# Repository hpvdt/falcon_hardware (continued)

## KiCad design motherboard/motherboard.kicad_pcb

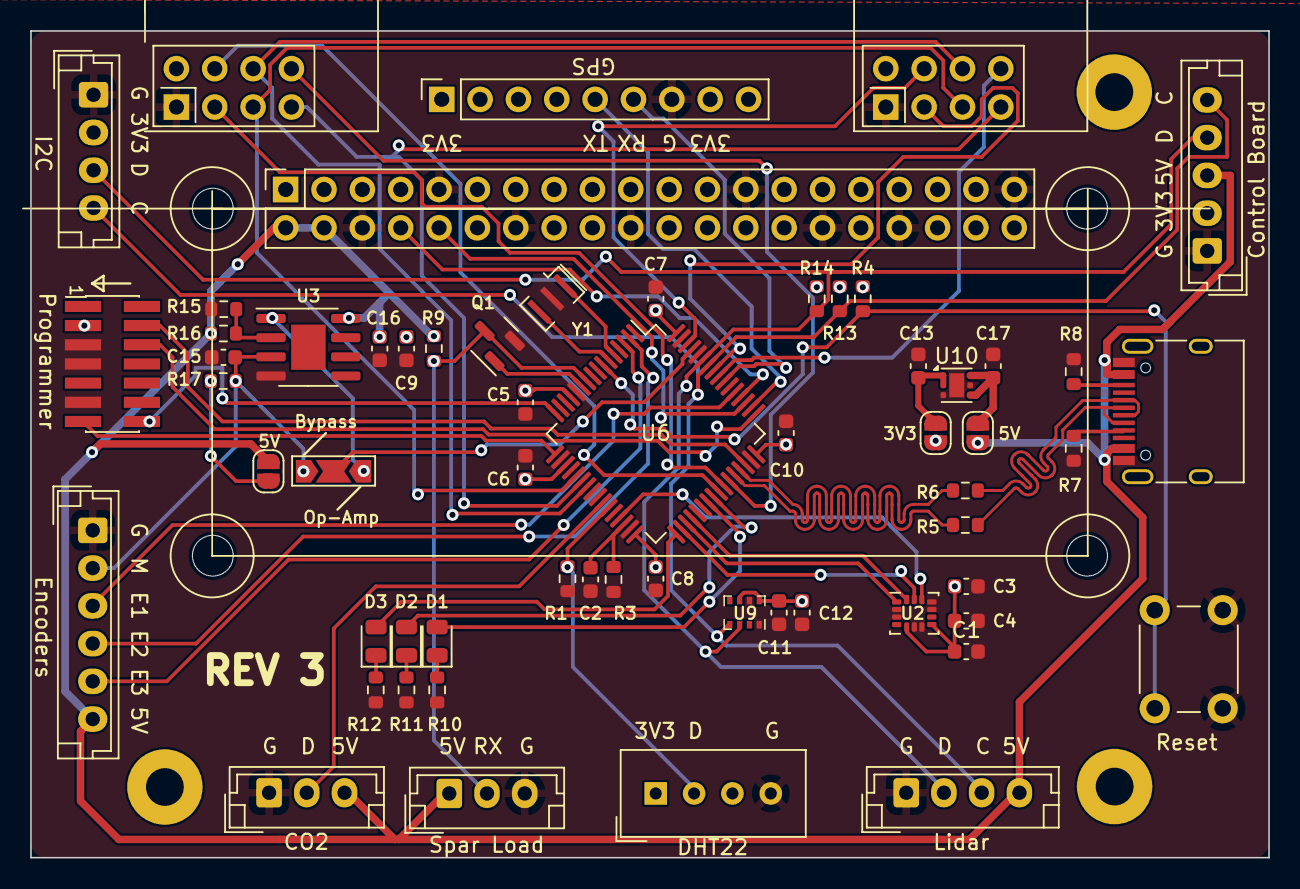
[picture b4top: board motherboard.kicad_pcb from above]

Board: 2 copper layers, 82.0 x 54.8 mm, 67 parts (0 on the bottom side), 56 nets.

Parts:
C1, C9, C15: 10n; C_0603_1608Metric
C2: 4.7u; C_0603_1608Metric
C3: 2.2u; C_0603_1608Metric
C4, C5, C6, C7, C8, C11, C12, C16: 100n; C_0603_1608Metric
C10: 1u; C_0603_1608Metric
C13, C17: 0.22u; C_0603_1608Metric
D1, D2, D3: LED; LED_0805_2012Metric
H1, H3, H4: MountingHole; MountingHole_2.5mm_Pad
H5, H6, H7, H8: MountingHole; MountingHole_2.7mm_M2.5
J1: Raspberry_Pi_2_3 ANT; PinSocket_2x20_P2.54mm_Vertical
J2: Conn_ST_STDC14; PinHeader_2x07_P1.27mm_Vertical_SMD
J3: Battery / Pitot/ Orientation; JST_EH_B4B-EH-A_1x04_P2.50mm_Vertical
J4: c02 censor; JST_EH_B3B-EH-A_1x03_P2.50mm_Vertical
J5: shaftencorder; JST_EH_B6B-EH-A_1x06_P2.50mm_Vertical
J6: USB_C_Receptacle_USB2.0; USB_C_Receptacle_HRO_TYPE-C-31-M-12
J7: SparLoad; JST_EH_B3B-EH-A_1x03_P2.50mm_Vertical
J8: lidar; JST_EH_B4B-EH-A_1x04_P2.50mm_Vertical
J9: Control Board; JST_EH_B5B-EH-A_1x05_P2.50mm_Vertical
JP1: Jumper_3_Open; SolderJumper-3_P2.0mm_Open_TrianglePad1.0x1.5mm_NumberLabels
JP4: 5V; SolderJumper-2_P1.3mm_Open_RoundedPad1.0x1.5mm
JP5, JP6: Jumper_2_Open; SolderJumper-2_P1.3mm_Open_RoundedPad1.0x1.5mm
Q1: 2N7002K; SOT-23
R1, R3: 100k; R_0603_1608Metric
R4, R13, R14: 10k; R_0603_1608Metric
R5, R6: 22R; R_0603_1608Metric
R7, R8: 5.1K; R_0603_1608Metric
R9: 5.6k; R_0603_1608Metric
R10, R11, R12: 130R; R_0603_1608Metric
R15: 1k; R_0603_1608Metric
R16: 20k; R_0603_1608Metric
R17: 470R; R_0603_1608Metric
SW1: MCU_RST; SW_PUSH_6mm_H4.3mm
U2: IMU; LGA-14_3x2.5mm_P0.5mm_LayoutBorder3x4y
U3: LM358; SOIC-8-1EP_3.9x4.9mm_P1.27mm_EP2.29x3mm
U4: GPS module; PinSocket_1x09_P2.54mm_Vertical
U5: DHT11(DHT22); Aosong_DHT11_5.5x12.0_P2.54mm
U6: STM32F412RETx; LQFP-64_10x10mm_P0.5mm
U7: nRF24L01-telemetry-INTERIOR; nRF24L01_Breakout
U8: nRF24L01-telemetry-EXTERIOR; nRF24L01_Breakout
U9: DPS310 - barometer; Bosch_LGA-8_2x2.5mm_P0.65mm_ClockwisePinNumbering
U10: TLV76733DRVx; WSON-6-1EP_2x2mm_P0.65mm_EP1x1.6mm
Y1: 8M; Resonator_SMD_Murata_CSTxExxV-3Pin_3.0x1.1mm

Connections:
+3.3V: C1.1, C3.1, C4.1, C5.2, C6.2, C7.2, C8.2, C9.2, C10.2, C11.1, C12.1, J2.3 (VCC), J3.2, J9.2, JP5.2 (B), R4.2, R13.1, R14.1, U2.5 (VDD_{IO}), U2.8 (VDD), U4.1 (3.3V), U4.8 (VIN), U5.1 (VDD), U6.13 (VDDA), U6.19 (VDD), U6.32 (VDD), U6.48 (VDD), U6.64 (VDD), U7.2 (VCC), U8.2 (VCC), U9.6 (V_{DDIO}), U9.8 (V_{DD})
+5V: C16.1, J1.2 (5V), J1.4 (5V), J4.3, J5.6, J6.A4 (VBUS), J6.A9 (VBUS), J6.B4 (VBUS), J6.B9 (VBUS), J7.1, J8.4, J9.3, JP4.2 (B), JP6.1 (A), R9.1, R16.1, U3.8 (V+)
/CO_{2}: J4.2, U6.26 (PB0)
/D+: J6.A6 (D+), J6.B6 (D+), R6.2
/D-: J6.A7 (D-), J6.B7 (D-), R5.2
/DHT22: R1.2, U5.2 (DATA), U6.27 (PB1)
/ENC1: J5.3, U6.53 (PC12)
/ENC2: J5.4, U6.2 (PC13)
/ENC3: J5.5, U6.3 (PC14)
/I2C_{SCK}: J3.4, J8.3, J9.5, R13.2, U6.58 (PB6), U9.4 (SCK)
/I2C_{SDA}: J3.3, J8.2, J9.4, R14.2, U6.59 (PB7), U9.3 (SDI)
/IMU_{CS}: U2.12 (CS), U6.29 (PB10)
/LED1: D1.2 (A), U6.39 (PC8)
/LED2: D2.2 (A), U6.40 (PC9)
/LED3: D3.2 (A), U6.33 (PB12)
/OneWire_{RX}: J7.2, Q1.3 (D), R9.2, U6.10 (PC2)
/OneWire_{TX}: Q1.1 (G), U6.11 (PC3)
/RST: R4.1, SW1.2, U6.7 (NRST)
/SHAFTENC IN: C15.1, J5.2, JP1.1 (A), R17.2, U3.3 (+)
/SHAFTENC OUT: JP1.2 (C), U6.61 (PB8)
/SPI1MISO: U6.22 (PA6), U7.7 (MISO), U8.7 (MISO)
/SPI1MOSI: U6.23 (PA7), U7.6 (MOSI), U8.6 (MOSI)
/SPI1SCK: U6.21 (PA5), U7.5 (SCK), U8.5 (SCK)
/SPI2MISO: U2.1 (SDO), U6.35 (PB14)
/SPI2MOSI: U2.14 (SDI), U6.36 (PB15)
/SPI2SCK: U2.13 (SCK), U6.34 (PB13)
/SWCLK: J2.6 (JCLK/SWCLK), U6.49 (PA14)
/SWDIO: J2.4 (JTMS/SWDIO), U6.46 (PA13)
/TELE_{CE}-E: U6.42 (PA9), U8.3 (CE)
/TELE_{CE}-int: U6.57 (PB5), U7.3 (CE)
/TELE_{CS}-E: U6.41 (PA8), U8.4 (~CSN)
/TELE_{CS}-int: U6.62 (PB9), U7.4 (~CSN)
/TELE_{IRQ}-E: U6.43 (PA10), U8.8 (IRQ)
/TELE_{IRQ}-int: U6.56 (PB4), U7.8 (IRQ)
/USART1_{RX}: U4.6 (RX), U6.55 (PB3)
/USART1_{TX}: U4.5 (TX), U6.50 (PA15)
/USART2_{RX}: J2.13 (VCP_RX), U6.17 (PA3)
/USART2_{TX}: J2.14 (VCP_TX), U6.16 (PA2)
/USART3_{RX}: J1.8 (GPIO14/TXD), U6.52 (PC11)
/USART3_{TX}: J1.10 (GPIO15/RXD), U6.51 (PC10)
/USB+: R6.1, U6.45 (PA12)
/USB-: R5.1, U6.44 (PA11)
GND: C1.2, C2.2, C3.2, C4.2, C5.1, C6.1, C7.1, C8.1, C9.1, C10.1, C11.2, C12.2, C13.2, C15.2, C16.2, C17.2, J1.6 (GND), J1.9 (GND), J1.14 (GND), J1.20 (GND), J1.25 (GND), J1.30 (GND), J1.34 (GND), J1.39 (GND), J2.5 (GND), J2.7 (GND), J2.11 (GNDDetect), J3.1, J4.1, J5.1, J6.A1 (GND), J6.A12 (GND), J6.B1 (GND), J6.B12 (GND), J7.3, J8.1, J9.1, Q1.2 (S), R1.1, R3.1, R7.1, R8.1, R10.1, R11.1, R12.2, R15.2, SW1.1, U2.2 (RESV), U2.3 (RESV), U2.6 (GND), U2.7 (RESV), U2.10 (RESV), U2.11 (RESV), U3.4 (V-), U4.7 (GND), U5.4 (GND), U6.12 (VSSA), U6.18 (VSS), U6.31 (VSS), U6.47 (VSS), U6.60 (BOOT0), U6.63 (VSS), U7.1 (GND), U8.1 (GND), U9.1 (GND), U9.7 (GND), U10.3 (GND), U10.5 (GND), U10.7 (PAD), Y1.2
unnamed: D1.1 (K), R10.2
unnamed: D2.1 (K), R11.2
unnamed: D3.1 (K), R12.1
unnamed: J6.A5 (CC1), R7.2
unnamed: J6.B5 (CC2), R8.2
unnamed: JP1.3 (B), U3.1
unnamed: JP4.1 (A), R17.1
unnamed: C13.1, JP5.1 (A), U10.1 (OUT), U10.2 (SNS)
unnamed: C17.1, JP6.2 (B), U10.4 (EN), U10.6 (IN)
unnamed: R15.1, R16.2, U3.2 (-)
unnamed: U6.5 (PH0), Y1.1
unnamed: U6.6 (PH1), Y1.3
unnamed: C2.1, R3.2, U6.30 (VCAP_1)

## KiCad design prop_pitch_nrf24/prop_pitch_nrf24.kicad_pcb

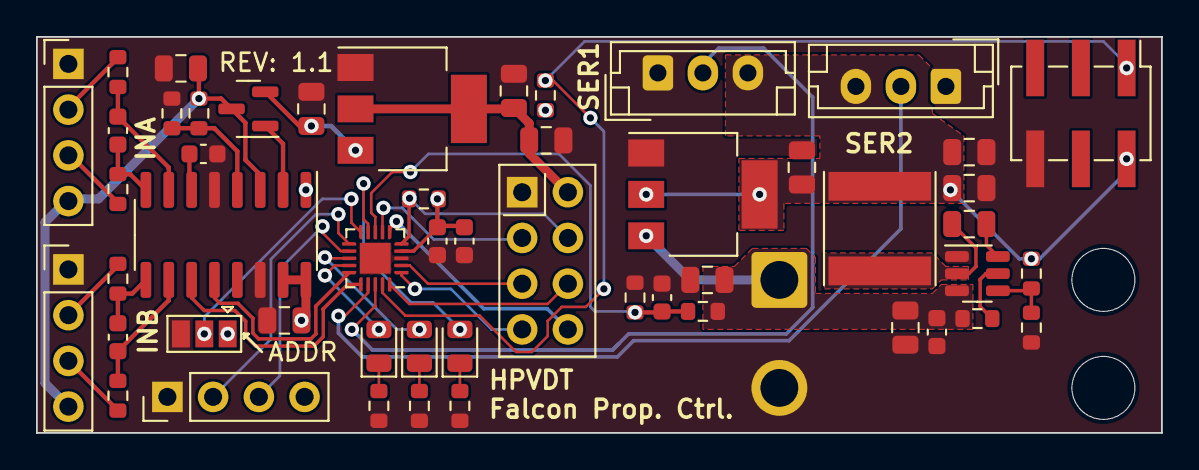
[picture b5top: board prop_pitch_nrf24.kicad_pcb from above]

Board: 2 copper layers, 62.5 x 22.0 mm, 53 parts (1 on the bottom side), 41 nets.

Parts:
BT1: Battery; SolderWire-1.5sqmm_1x02_P6mm_D1.7mm_OD3mm_Relief
C1, C2, C3, C5, C9, C11: 100n; C_0603_1608Metric
C4, C6, C10, C15, C16, C18: 10u; C_0805_2012Metric
C7: 10n; C_0603_1608Metric
C12: 100n; C_0805_2012Metric
C13, C14, C19, C20: 22u; C_0805_2012Metric
D1, D2, D3: LED; LED_0805_2012Metric
J1: LOAD1; PinHeader_1x04_P2.54mm_Vertical
J2: LOAD2; PinHeader_1x04_P2.54mm_Vertical
J3: AVR-UPDI-6; PinHeader_2x03_P2.54mm_Vertical_SMD
J4: SERVO2; JST_EH_B3B-EH-A_1x03_P2.50mm_Vertical
J5: SERVO1; JST_EH_B3B-EH-A_1x03_P2.50mm_Vertical
J6: SERIAL; PinHeader_1x04_P2.54mm_Vertical
JP1: ADDRESS; SolderJumper-3_P1.3mm_Open_Pad1.0x1.5mm
L1: 3u3; L_Taiyo-Yuden_NR-60xx
Q1: MMSS8550; SOT-23
R1, R2, R3: 430; R_0603_1608Metric
R4, R5, R6, R7: 100; R_0603_1608Metric
R8: 15k; R_0603_1608Metric
R9, R12, R13, R14, R16: 10k; R_0603_1608Metric
R10: 20k; R_0603_1608Metric
R11: 8.2k; R_0603_1608Metric
R15: 54k9; R_0603_1608Metric
U1: ATtiny1616-M; VQFN-20-1EP_3x3mm_P0.4mm_EP1.7x1.7mm
U2: HX711; SOP-16_3.9x9.9mm_P1.27mm
U3: TPS563208DDCR; TSOT-23-6
U4: AZ1117-5.0; SOT-223-3_TabPin2
U5: AZ1117-3.3; SOT-223-3_TabPin2
U6: NRF24L01_Breakout; nRF24L01_Breakout

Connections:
+3.3VA: C6.2, J1.4, J2.4, Q1.3 (C), R10.1, U2.3 (AVDD)
+3V3: C18.2, C20.2, U5.2 (VO), U6.2 (VCC)
+5V: C4.2, C5.1, C7.1, C13.2, C14.2, C16.2, C19.2, J3.2 (VCC), J4.3, J5.3, J6.4, JP1.1 (A), L1.2, Q1.2 (E), R12.1, R13.1, R15.1, U1.4 (VCC), U2.1 (VSUP), U2.15 (RATE), U2.16 (DVDD), U4.2 (VO), U5.3 (VI)
+BATT: BT1.1 (+), C10.2, C11.2, C15.2, R8.1, R14.1, U3.3 (VIN), U4.3 (VI)
/ADDRESS: JP1.2 (C), U1.10 (PB4)
/BASE: Q1.1 (B), U2.2 (BASE)
/BATT_{SCALED}: C3.1, R8.2, R9.1, U1.8 (PA7)
/CE_{nRF}: U1.7 (PA6), U6.3 (CE)
/DOUT_{AMP}: U1.15 (PC0), U2.12 (DOUT)
/FB: R15.2, R16.2, U3.4 (VFB)
/FB_{VA}: R10.2, R11.1, U2.4 (VFB)
/INA+: C1.2, R4.2, U2.8 (INA+)
/INA-: C1.1, R5.2, U2.7 (INA-)
/INB+: C2.2, R6.2, U2.10 (INB+)
/INB-: C2.1, R7.2, U2.9 (INB-)
/INT_{nRF}: U1.6 (PA5), U6.8 (IRQ)
/LED_{1}: D1.2 (A), U1.14 (PB0)
/LED_{2}: D2.2 (A), U1.13 (PB1)
/LED_{3}: D3.2 (A), U1.9 (PB5)
/MISO: U1.1 (PA2), U6.7 (MISO)
/MOSI: U1.20 (PA1), U6.6 (MOSI)
/RX: J6.2, U1.11 (PB3)
/S+_{LC1}: J1.3, R4.1
/S+_{LC2}: J2.3, R6.1
/S-_{LC1}: J1.2, R5.1
/S-_{LC2}: J2.2, R7.1
/SCK: U1.2 (PA3), U6.5 (SCK)
/SCK_{AMP}: U1.16 (PC1), U2.11 (PD_SCK)
/SERVO_{1}: J5.2, U1.18 (PC3)
/SERVO_{2}: J4.2, U1.17 (PC2)
/TX: J6.3, U1.12 (PB2)
/~CS_{nRF}: R13.2, U1.5 (PA4), U6.4 (~CSN)
/~RESET: J3.1 (DATA), R12.2, U1.19 (~RESET/PA0)
GND: BT1.2 (-), C3.2, C4.1, C5.2, C6.1, C7.2, C9.1, C10.1, C11.1, C13.1, C14.1, C15.1, C16.1, C18.1, C19.1, C20.1, J1.1, J2.1, J3.6 (GND), J4.1, J5.1, J6.1, JP1.3 (B), R1.2, R2.2, R3.2, R9.2, R11.2, R16.1, U1.3 (GND), U1.21 (GND), U2.5 (AGND), U2.14 (XI), U3.1 (GND), U4.1 (GND), U5.1 (GND), U6.1 (GND)
unnamed: D1.1 (K), R1.1
unnamed: D2.1 (K), R2.1
unnamed: D3.1 (K), R3.1
unnamed: C9.2, U2.6 (VBG)
unnamed: R14.2, U3.5 (EN)
unnamed: C12.2, L1.1, U3.2 (SW)
unnamed: C12.1, U3.6 (VBST)

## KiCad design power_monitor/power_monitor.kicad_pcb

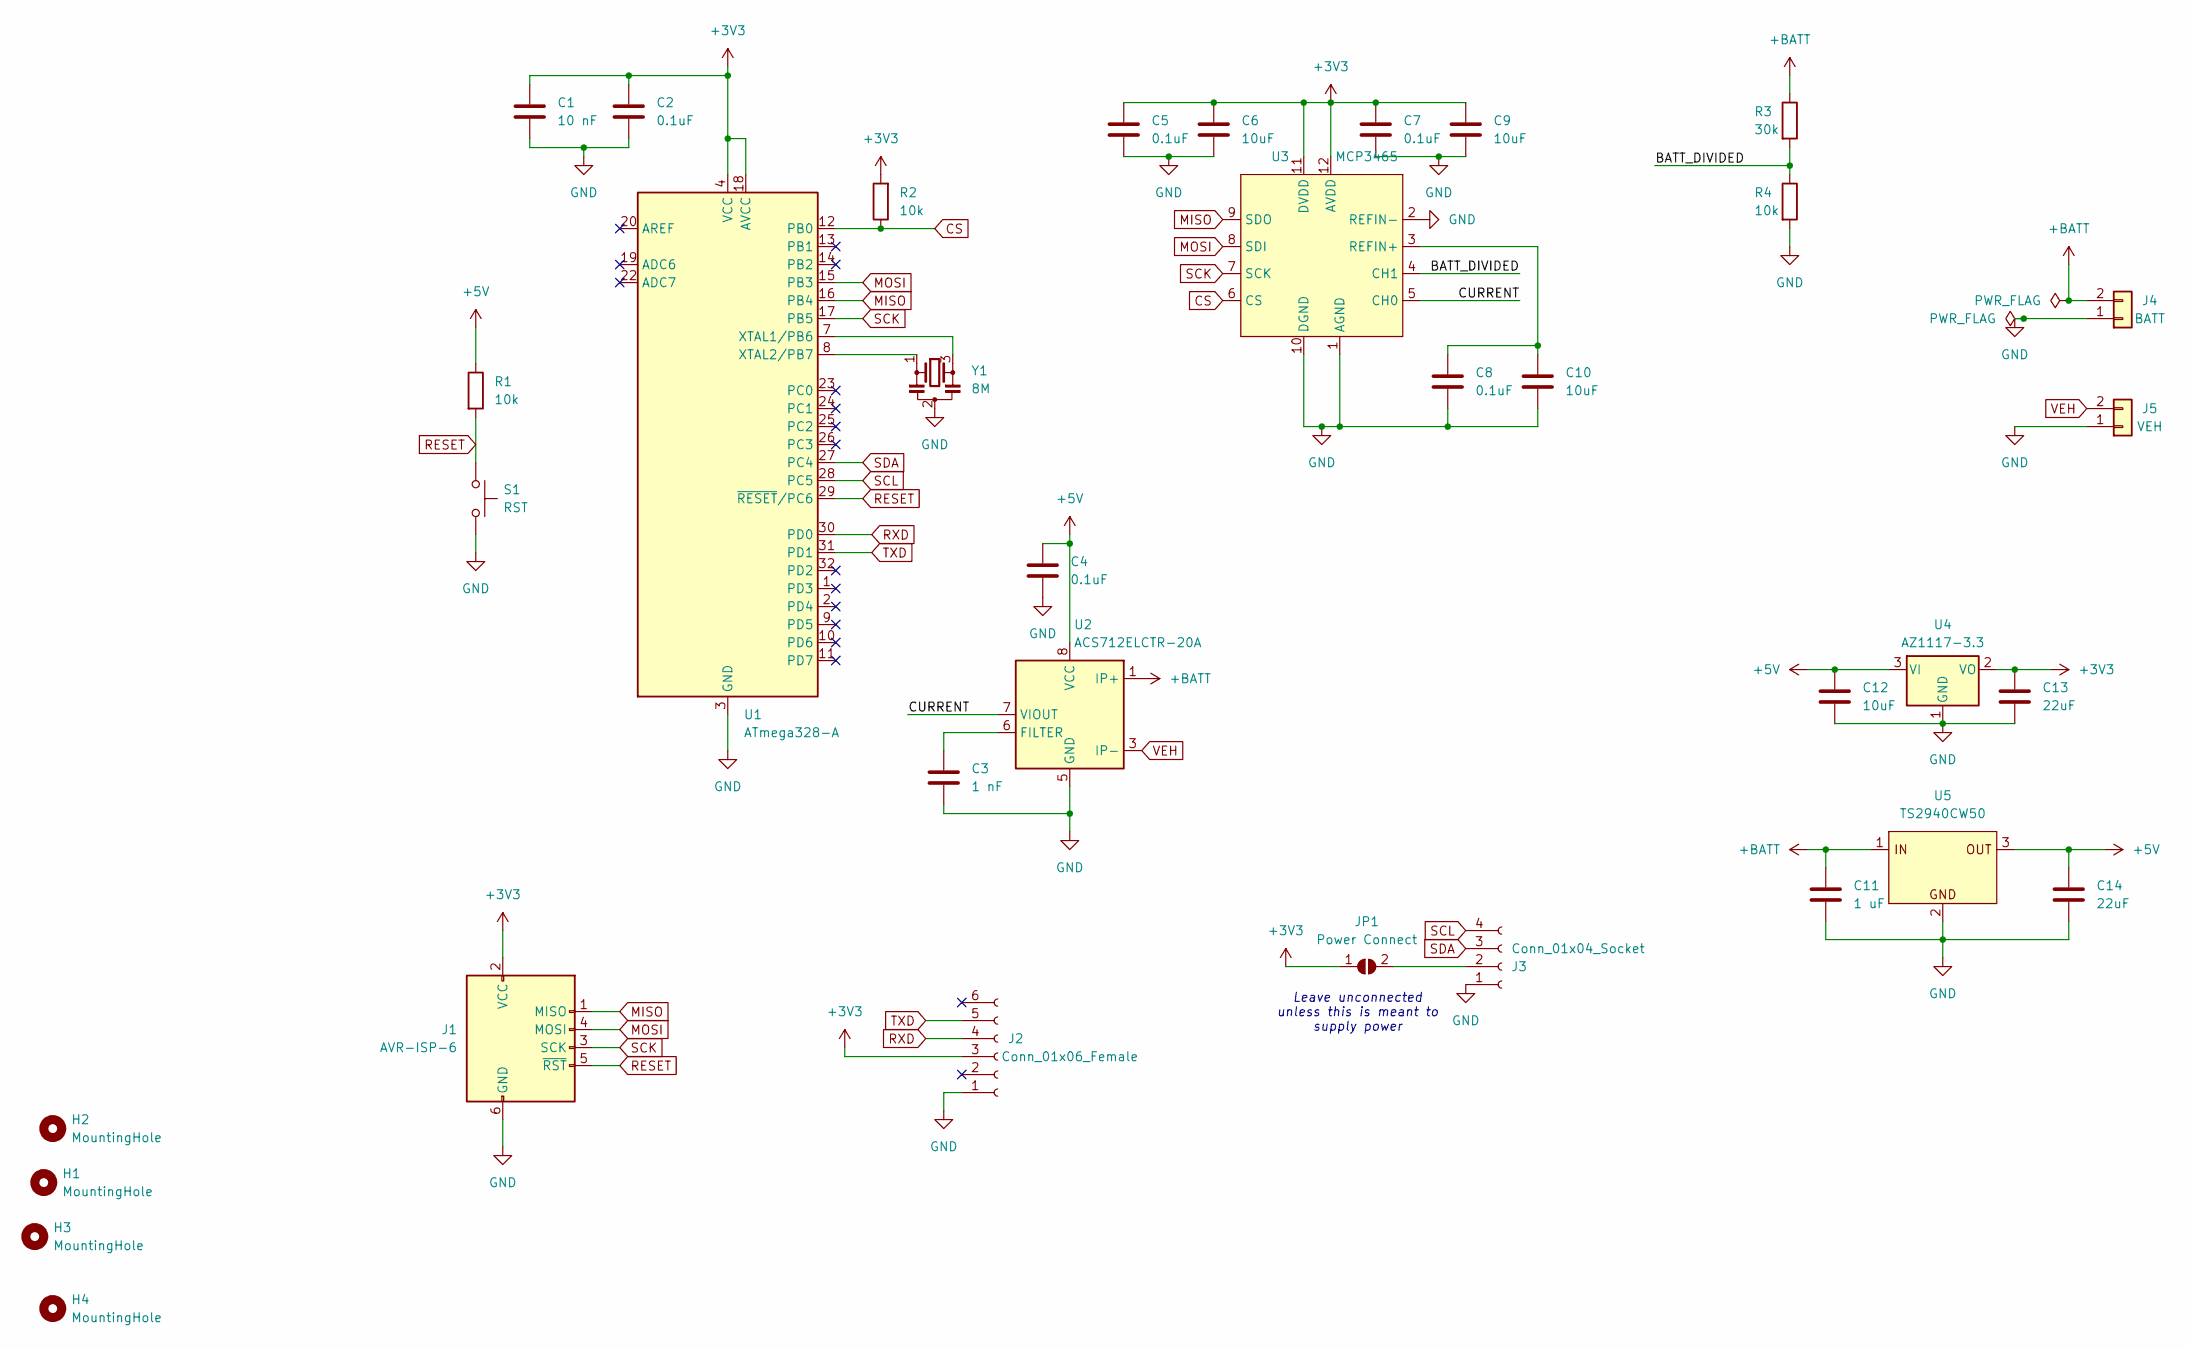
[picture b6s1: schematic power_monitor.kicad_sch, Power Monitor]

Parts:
C1: 10 nF; C_0603_1608Metric
C2, C4, C5, C7, C8: 0.1uF; C_0603_1608Metric
C3: 1 nF; C_0603_1608Metric
C6, C9, C10, C12: 10uF; C_0805_2012Metric
C11: 1 uF; C_0603_1608Metric
C13, C14: 22uF; C_0805_2012Metric
H1, H2, H3, H4: MountingHole; MountingHole_3.2mm_M3_ISO14580
J1: AVR-ISP-6; PinHeader_2x03_P2.54mm_Vertical_SMD
J2: Conn_01x06_Female; PinHeader_1x06_P2.54mm_Vertical
J3: Conn_01x04_Socket; JST_XA_B04B-XASK-1_1x04_P2.50mm_Vertical
J4: BATT; AMASS_XT60-M_1x02_P7.20mm_Vertical
J5: VEH; AMASS_XT60-F_1x02_P7.20mm_Vertical
JP1: Power Connect; SolderJumper-2_P1.3mm_Open_Pad1.0x1.5mm
R1, R2, R4: 10k; R_0603_1608Metric
R3: 30k; R_0603_1608Metric
S1: RST; SW_SPST_SKQG_WithStem
U1: ATmega328-A; TQFP-32_7x7mm_P0.8mm
U2: ACS712ELCTR-20A; SOIC-8_3.9x4.9mm_P1.27mm
U3: MCP3465; QFN-12_EP_2x2_Pitch0.4mm
U4: AZ1117-3.3; SOT-223-3_TabPin2
U5: TS2940CW50; SOT-223-3_TabPin2
Y1: 8M; Resonator_SMD_Murata_CSTxExxV-3Pin_3.0x1.1mm

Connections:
+3V3: C1.1, C2.1, C5.1, C6.1, C7.1, C9.1, C13.1, J1.2 (VCC), J2.3, JP1.1 (A), R2.2, U1.4 (VCC), U1.6 (VCC), U1.18 (AVCC), U3.11 (DVDD), U3.12 (AVDD), U4.2 (VO)
+5V: C4.1, C12.1, C14.1, R1.1, U2.8 (VCC), U4.3 (VI), U5.3
+BATT: C11.1, J4.2, R3.1, U2.1 (IP+), U2.2 (IP+), U5.1
/BATT_DIVIDED: R3.2, R4.1, U3.4 (CH1)
/CURRENT: U2.7 (VIOUT), U3.5 (CH0)
CS: R2.1, U1.12 (PB0), U3.6 (CS)
GND: C1.2, C2.2, C3.2, C4.2, C5.2, C6.2, C7.2, C8.2, C9.2, C10.2, C11.2, C12.2, C13.2, C14.2, J1.6 (GND), J2.1, J3.1, J4.1, J5.1, R4.2, S1.2, U1.3 (GND), U1.5 (GND), U1.21 (GND), U2.5 (GND), U3.1 (AGND), U3.2 (REFIN-), U3.10 (DGND), U3.13 (EP), U4.1 (GND), U5.2, Y1.2
MISO: J1.1 (MISO), U1.16 (PB4), U3.9 (SDO)
MOSI: J1.4 (MOSI), U1.15 (PB3), U3.8 (SDI)
unnamed: J3.2, JP1.2 (B)
unnamed: U1.7 (XTAL1/PB6), Y1.3
unnamed: U1.8 (XTAL2/PB7), Y1.1
unnamed: C3.1, U2.6 (FILTER)
unnamed: C8.1, C10.1, U3.3 (REFIN+)
RESET: J1.5 (~RST), R1.2, S1.1, U1.29 (~RESET/PC6)
RXD: J2.4, U1.30 (PD0)
SCK: J1.3 (SCK), U1.17 (PB5), U3.7 (SCK)
SCL: J3.4, U1.28 (PC5)
SDA: J3.3, U1.27 (PC4)
TXD: J2.5, U1.31 (PD1)
VEH: J5.2, U2.3 (IP-), U2.4 (IP-)

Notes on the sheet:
Leave unconnected unless this is meant to supply power

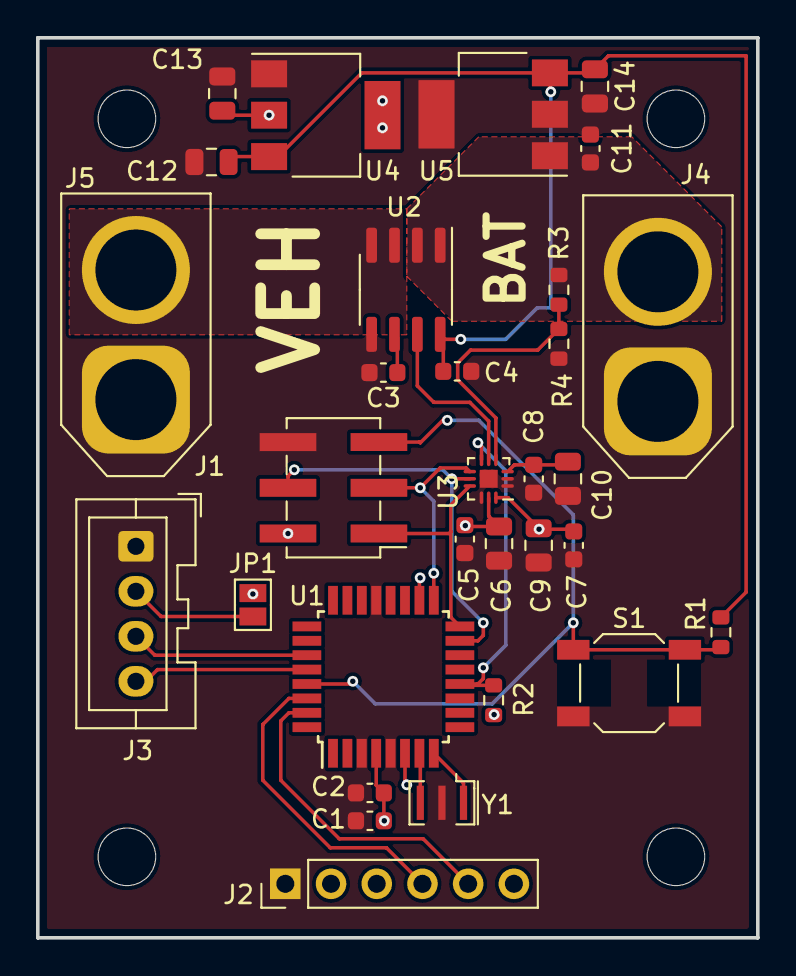
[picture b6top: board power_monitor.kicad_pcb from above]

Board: 2 copper layers, 40.0 x 50.0 mm, 35 parts (0 on the bottom side), 21 nets.

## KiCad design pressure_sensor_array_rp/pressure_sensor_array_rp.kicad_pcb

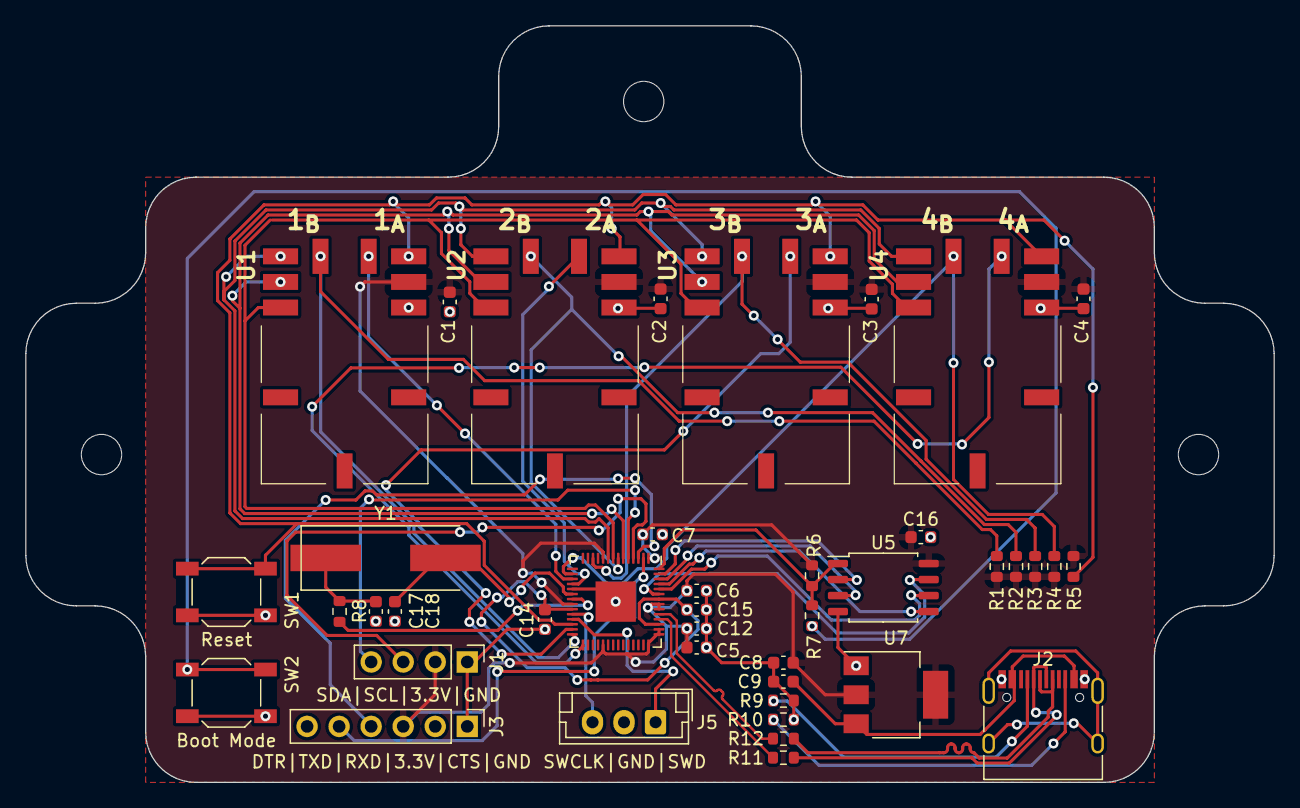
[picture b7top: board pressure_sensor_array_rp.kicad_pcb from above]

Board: 2 copper layers, 99.0 x 60.0 mm, 44 parts (0 on the bottom side), 38 nets.

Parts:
C1, C2, C3, C4, C5, C6, C7, C14, C16: 100n; C_0603_1608Metric
C8, C9: 22u; C_0603_1608Metric
C12, C15: 1n; C_0603_1608Metric
C17, C18: 27p; C_0603_1608Metric
H1, H2, H3: MountingHole; MountingHole_3.2mm_M3
J1: Conn_01x04_Pin; PinHeader_1x04_P2.54mm_Vertical
J2: USB_C_Receptacle_USB2.0; USB_C_Receptacle_HRO_TYPE-C-31-M-12
J3: Conn_01x06_Pin; PinHeader_1x06_P2.54mm_Vertical
J5: Conn_01x03_Pin; JST_EH_B3B-EH-A_1x03_P2.50mm_Vertical
R1, R2, R3, R4, R5, R6: 10k; R_0603_1608Metric
R7, R8: 1k; R_0603_1608Metric
R9, R10: 5.1k; R_0603_1608Metric
R11, R12: 22; R_0603_1608Metric
SW1: Reset; SW_SPST_SKQG_WithStem
SW2: Boot Mode; SW_SPST_SKQG_WithStem
U1, U2, U3, U4: HV120SM02C
U5: W25Q128JVS; SOIC-8_5.23x5.23mm_P1.27mm
U6: RP2040; QFN-56-1EP_7x7mm_P0.4mm_EP3.2x3.2mm
U7: AZ1117-3.3; SOT-223-3_TabPin2
Y1: Crystal; Crystal_SMD_HC49-SD(ABLS-12.000MHZ-B4-T)

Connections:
+1V1: C14.1, C15.1, U6.23 (DVDD), U6.45 (VREG_VOUT), U6.50 (DVDD)
+3.3V: C1.1, C2.1, C3.1, C4.1, C5.1, C6.1, C7.1, C8.2, C12.1, C16.1, J1.2, J3.3, R1.2, R2.2, R3.2, R4.2, R5.1, R6.1, U1.9 (VDD), U2.9 (VDD), U3.9 (VDD), U4.9 (VDD), U5.8 (VCC), U6.1 (IOVDD), U6.10 (IOVDD), U6.22 (IOVDD), U6.33 (IOVDD), U6.42 (IOVDD), U6.43 (ADC_AVDD), U6.44 (VREG_IN), U6.48 (USB_VDD), U6.49 (IOVDD), U7.2 (VO)
+5V: C9.2, J2.A4 (VBUS), J2.A9 (VBUS), J2.B4 (VBUS), J2.B9 (VBUS), U7.3 (VI)
/D+: J2.A6 (D+), J2.B6 (D+), R12.1
/D-: J2.A7 (D-), J2.B7 (D-), R11.1
/DAV_{1}: U1.11 (DAV), U6.17 (GPIO14)
/DAV_{2}: U2.11 (DAV), U6.18 (GPIO15)
/DAV_{3}: U3.11 (DAV), U6.27 (GPIO16)
/DAV_{4}: U4.11 (DAV), U6.29 (GPIO18)
/MISO: U1.3 (MISO), U2.3 (MISO), U3.3 (MISO), U4.3 (MISO), U6.6 (GPIO4)
/MOSI: U1.2 (MOSI), U2.2 (MOSI), U3.2 (MOSI), U4.2 (MOSI), U6.9 (GPIO7)
/QSPI_SCLK: U5.6 (CLK), U6.52 (QSPI_SCLK)
/QSPI_SD0: U5.5 (DI(IO0)), U6.53 (QSPI_SD0)
/QSPI_SD1: U5.2 (DO(IO1)), U6.55 (QSPI_SD1)
/QSPI_SD2: U5.3 (IO2), U6.54 (QSPI_SD2)
/QSPI_SD3: U5.7 (IO3), U6.51 (QSPI_SD3)
/QSPI_SS: R6.2, R7.1, U5.1 (~CS), U6.56 (QSPI_SS)
/RXD: J3.4, U6.3 (GPIO1)
/SCK: U1.4 (SCK), U2.4 (SCK), U3.4 (SCK), U4.4 (SCK), U6.8 (GPIO6)
/SCL: J1.4, U6.5 (GPIO3)
/SDA: J1.3, U6.4 (GPIO2)
/SWCLK: J5.3, U6.24 (SWCLK)
/SWD: J5.1, U6.25 (SWD)
/TXD: J3.5, U6.2 (GPIO0)
/USB_BOOT: R7.2, SW2.2
/USB_D+: R12.2, U6.47 (USB_DP)
/USB_D-: R11.2, U6.46 (USB_DM)
/nRST: R5.2, SW1.2, U1.10 (nRST), U2.10 (nRST), U3.10 (nRST), U4.10 (nRST), U6.26 (RUN)
/nSS_{1}: R1.1, U1.1 (nSS), U6.28 (GPIO17)
/nSS_{2}: R2.1, U2.1 (nSS), U6.7 (GPIO5)
/nSS_{3}: R3.1, U3.1 (nSS), U6.12 (GPIO9)
/nSS_{4}: R4.1, U4.1 (nSS), U6.16 (GPIO13)
GND: C1.2, C2.2, C3.2, C4.2, C5.2, C6.2, C7.2, C8.1, C9.1, C12.2, C14.2, C15.2, C16.2, C17.1, C18.1, J1.1, J2.A1 (GND), J2.A12 (GND), J2.B1 (GND), J2.B12 (GND), J3.1, J5.2, R9.2, R10.2, SW1.1, SW2.1, U1.8 (GND), U2.8 (GND), U3.8 (GND), U4.8 (GND), U5.4 (GND), U6.19 (TESTEN), U6.57 (GND), U7.1 (GND)
unnamed: C17.2, R8.1, Y1.1
unnamed: J2.A5 (CC1), R9.1
unnamed: J2.B5 (CC2), R10.1
unnamed: C18.2, U6.20 (XIN), Y1.2
unnamed: R8.2, U6.21 (XOUT)

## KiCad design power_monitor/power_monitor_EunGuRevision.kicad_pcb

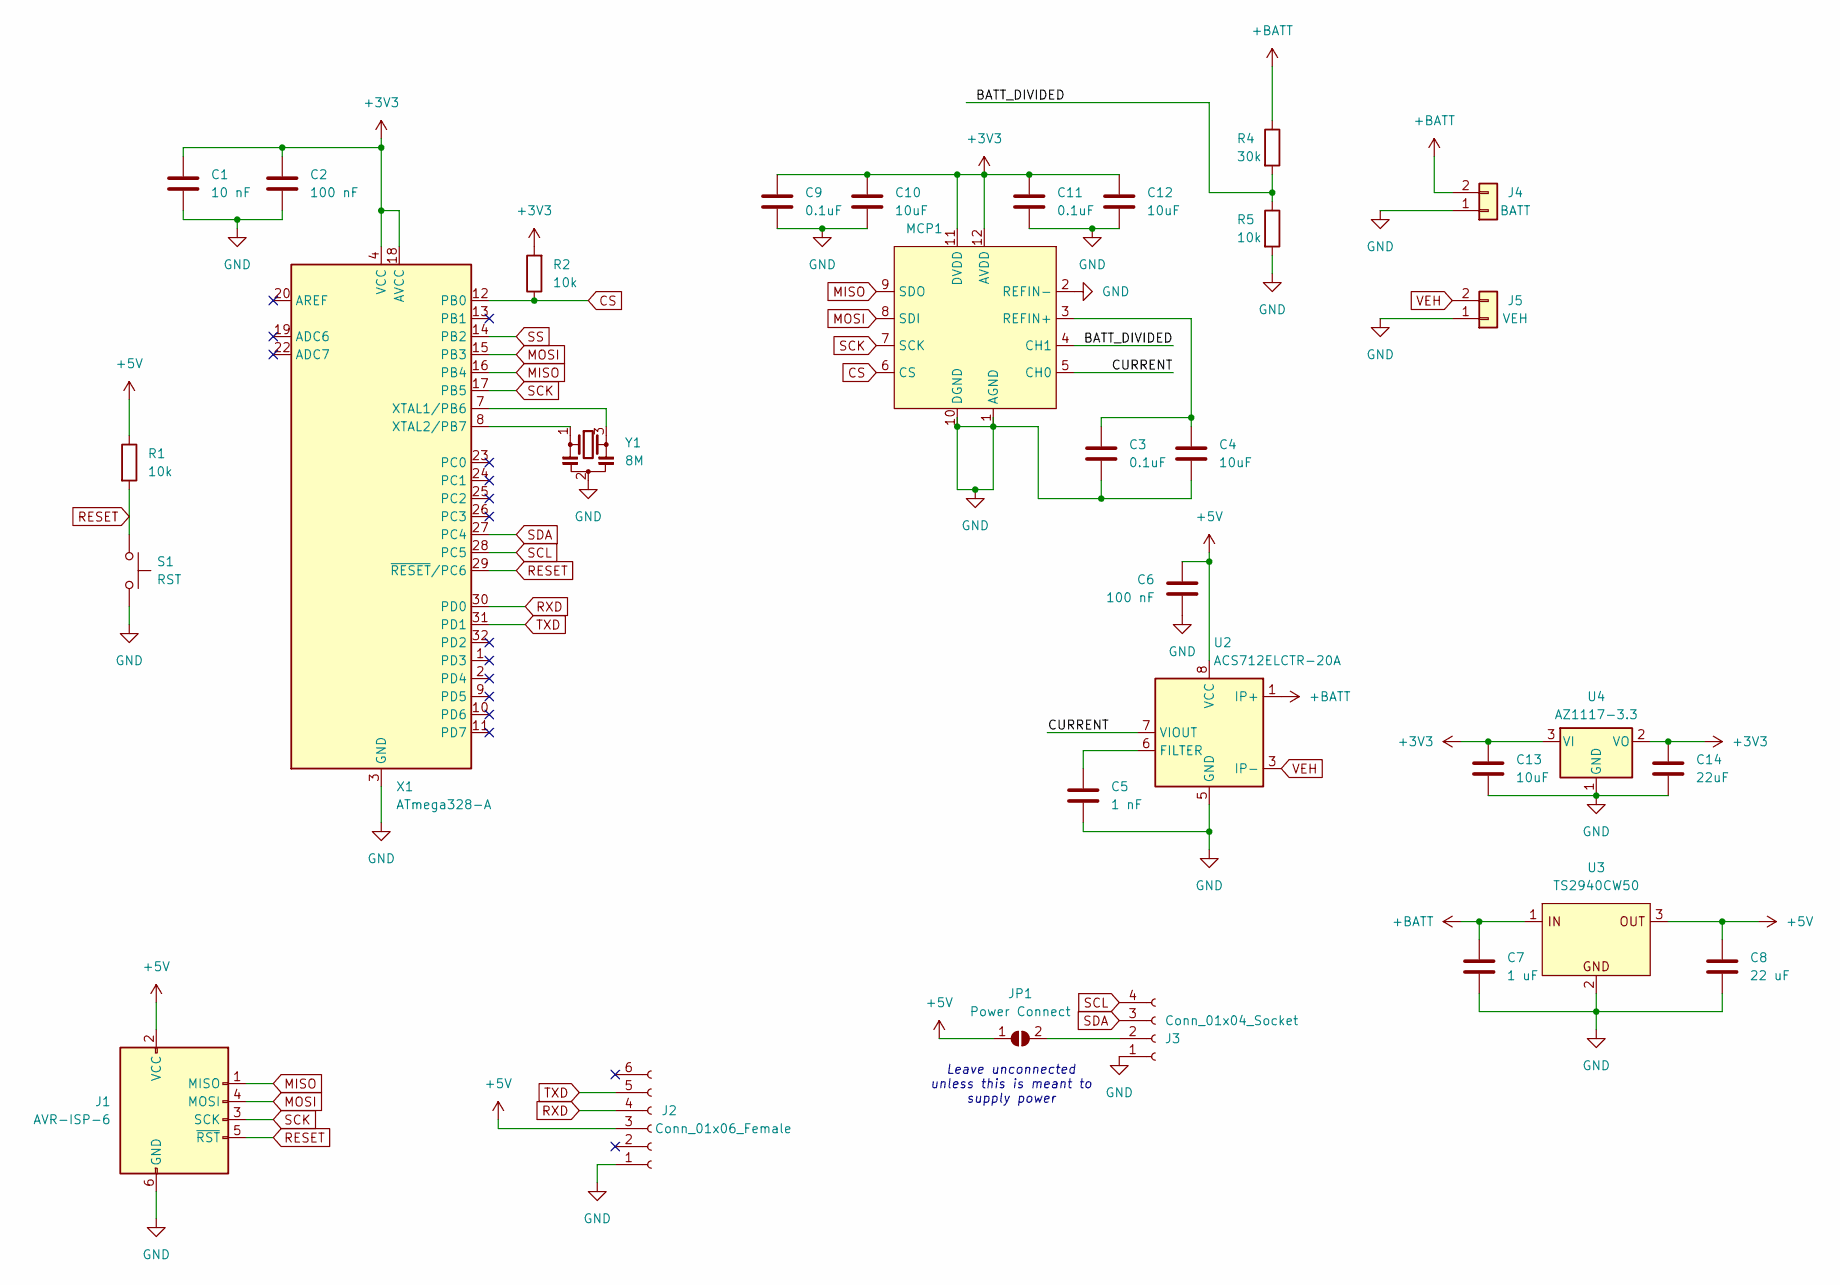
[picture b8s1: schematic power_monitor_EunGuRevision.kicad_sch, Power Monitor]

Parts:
C1: 10 nF; C_0603_1608Metric
C2, C6: 100 nF; C_0603_1608Metric
C3, C9, C11: 0.1uF; C_0603_1608Metric
C4, C10, C12, C13: 10uF; C_0805_2012Metric
C5: 1 nF; C_0603_1608Metric
C7: 1 uF; C_0603_1608Metric
C8: 22 uF; C_0805_2012Metric
C14: 22uF; C_0805_2012Metric
J1: AVR-ISP-6; PinHeader_2x03_P2.54mm_Vertical_SMD
J2: Conn_01x06_Female; PinHeader_1x06_P2.54mm_Vertical
J3: Conn_01x04_Socket; JST_XA_B04B-XASK-1_1x04_P2.50mm_Vertical
J4: BATT; AMASS_XT60-F_1x02_P7.20mm_Vertical
J5: VEH; AMASS_XT60-M_1x02_P7.20mm_Vertical
JP1: Power Connect; SolderJumper-2_P1.3mm_Open_Pad1.0x1.5mm
MCP1: QFN-12_EP_2x2_Pitch0.4mm
R1, R2, R5: 10k; R_0603_1608Metric
R4: 30k; R_0603_1608Metric
S1: RST; SW_SPST_SKQG_WithStem
U2: ACS712ELCTR-20A; SOIC-8_3.9x4.9mm_P1.27mm
U3: TS2940CW50; SOT-223-3_TabPin2
U4: AZ1117-3.3; SOT-223-3_TabPin2
X1: ATmega328-A; TQFP-32_7x7mm_P0.8mm
Y1: 8M; Resonator_SMD_Murata_CSTxExxV-3Pin_3.0x1.1mm

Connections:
+3V3: C1.1, C2.1, C9.1, C10.1, C11.1, C12.1, C13.1, C14.1, MCP1.11 (DVDD), MCP1.12 (AVDD), R2.2, U4.2 (VO), U4.3 (VI), X1.4 (VCC), X1.6 (VCC), X1.18 (AVCC)
+5V: C6.1, C8.1, J1.2 (VCC), J2.3, JP1.1 (A), R1.1, U2.8 (VCC), U3.3
+BATT: C7.1, J4.2, R4.1, U2.1 (IP+), U2.2 (IP+), U3.1
/BATT_DIVIDED: MCP1.4 (CH1), R4.2, R5.1
/CURRENT: MCP1.5 (CH0), U2.7 (VIOUT)
CS: MCP1.6 (CS), R2.1, X1.12 (PB0)
GND: C1.2, C2.2, C3.2, C4.2, C5.2, C6.2, C7.2, C8.2, C9.2, C10.2, C11.2, C12.2, C13.2, C14.2, J1.6 (GND), J2.1, J3.1, J4.1, J5.1, MCP1.1 (AGND), MCP1.2 (REFIN-), MCP1.10 (DGND), R5.2, S1.2, U2.5 (GND), U3.2, U4.1 (GND), X1.3 (GND), X1.5 (GND), X1.21 (GND), Y1.2
MISO: J1.1 (MISO), MCP1.9 (SDO), X1.16 (PB4)
MOSI: J1.4 (MOSI), MCP1.8 (SDI), X1.15 (PB3)
unnamed: J3.2, JP1.2 (B)
unnamed: C3.1, C4.1, MCP1.3 (REFIN+)
unnamed: C5.1, U2.6 (FILTER)
unnamed: X1.7 (XTAL1/PB6), Y1.3
unnamed: X1.8 (XTAL2/PB7), Y1.1
RESET: J1.5 (~RST), R1.2, S1.1, X1.29 (~RESET/PC6)
RXD: J2.4, X1.30 (PD0)
SCK: J1.3 (SCK), MCP1.7 (SCK), X1.17 (PB5)
SCL: J3.4, X1.28 (PC5)
SDA: J3.3, X1.27 (PC4)
SS: X1.14 (PB2)
TXD: J2.5, X1.31 (PD1)
VEH: J5.2, U2.3 (IP-), U2.4 (IP-)

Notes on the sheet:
Leave unconnected unless this is meant to supply power

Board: 2 copper layers, 31 parts (0 on the bottom side), 21 nets, no tracks yet.

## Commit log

2023-07-01 Inital hardware file upload
2023-07-12 added ND005 sensors to bill of materials.
2023-07-12 Touched up spar sensor to reflect parts as ordered
2023-07-13 Updated spar sensor to reflect order
2023-07-13 Adjusted pullup resistors
2023-07-13 Added BOM for servo regulator
2023-07-13 Updated for prop pitch order
2023-07-13 Changed indicator resistor values
2023-07-13 Upgraded STM32
2023-07-13 Uploading BOM for main board
2023-07-21 Added spar sensor BOM
2023-07-21 Initial commit of power monitoring system
2023-07-21 Touched up schematic
2023-07-21 Set footprints, touched up regulator symbol
2023-07-21 Readded spar sensor BOM
2023-07-27 Preliminary block diagram
2023-07-27 Reduced block diagram colouring
2023-07-27 Removed lock files
2023-07-27 Excluding lock files in git
2023-08-02 Updated block diagram
2023-08-03 Add files via upload
    I am so confused I'm not sure I ever understood how to understand this stuff :). Also never used GitHub bfr so hopefully this is the right way to share edits
2023-08-04 Finished schematic
    Updated with new ADC and added voltage regulator
2023-08-04 BOOM
    Added footprints
2023-08-08 PCB Arrangement
    uh Savo how do I do this. I just grouped everything that needed to be together but I didn't fully finish. Also I'll send it over discord in case this isn't the right one
2023-08-09 Touched up schematic and initial layout
2023-08-11 Added symbol library
    yes
2023-08-11 Initial upload of motherboard
2023-08-15 PCB Layout
    Created initial PCB layout and included more complicated connections to give an idea of what's going on. There's a connection that goes under the board since my brain does not know how to rearrange t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
2023-08-18 PCB Layout finished
    HAHAHAHAHA IT'S DONE. will commence routing.
2023-08-18 Added CO2 sensor to block diagram
2023-08-18 Preliminary routing
    Rough ideas for routing. Didn't do any ground connections yet.
2023-08-19 Added datasheet link for regulator
2023-08-23 Removed alternate prop pitch for development in another branch
2023-08-23 haHA
    Routing :D
    Silkscreen :\
2023-08-23 Done
    Completed functional layout - savo
2023-08-23 Initial upload of redesigned prop controller
2023-08-23 Added serial header and address jumper
2023-08-25 Add new connections
    Added UART and SPI Pin connections
2023-08-25 Reverted to default sheet template
2023-09-12 Bro where is my last update
    Added a name and some author stuff
2023-09-12 More pretty edits
    Now that I know what the layers really are it makes a lot more sense
2023-09-14 Labels
    Made em bigger.
2023-09-15 pls let this end
    label. bigger.
2023-09-16 Small edits
    Moved around the text on back and moved the trace by the mounting hole.
2023-09-22 Motherboard I/O streams
2023-09-23 insertion of imu, gps, telemetery, etc.
2023-11-01 Adding Components to motherboard
    Added HC-05 and MH-Z19 To the motherboard schematic
2023-11-09 Completed First Draft of Motherboard Schematic
    Added in second bluetooth module, corrected pin allocations, fixed schematic symbols
2023-11-10 Edited Headers added power and ground pins to external board headers, added ground to MC, added capictor to I2C
2023-11-10 Added power to output headers
2023-11-10 Fixed up some schmatic symbols
    Fixed schematic symbols for hc-05 and the 6 axis IMU
2023-11-10 Final motherboard schematic draft
    Made several small changes to the schematic:
    - Merged all custom symbols into one library
    - Touched up custom symbols for aesthetics and organization
    - Adjusted schematic for revised schematics
    - Added OneWire hardware to schematic
    - Removed redudant 3.3V regulator (3.3V will be supplied by control board)
2023-11-19 FootPrints assigned
    Assigned resistor and capacitor footprints
2023-11-20 Completed Footprint Draft
    Added pin headers for all the remaining components on the board.
2023-11-25 Placed footprints
    Footprints must still be edited
2023-11-25 Edited footprints
    Edited custom footprints and completed first layout draft
2023-11-25 Revised hardware
2023-11-28 Added Traces
    Added more traces to the layout
2023-11-29 Completed draft 1 of layout
    Finished laying down traces and running drc on the layout
2023-11-29 Touch ups for control board
    - Made adjustments to the placement of the decoupling capacitors for the STM32.
    - Rotated some capacitors for VBATT pour
    - Removed reference designators for most components
    - Added some labels for the main power headers
2023-11-29 Touched up labels and title block
2023-11-29 Polished 1st Draft Layout
    Aligned vias, grouped traces, added text and graphics
2023-11-29 V3 Block Diagram, nRF24s
2023-11-29 V3 Block Diagram, jpg
2023-11-30 added name, title, company, revision # & authors
2023-11-30 Completed feedback for draft 1 round 1
    addded thicker traces, disconnected 3.3V from RPi, changed capacitor location, added mounting holes for RPi, added mounting holes to the board, added programming labels
2023-11-30 Create #auto_saved_files#
2023-11-30 Removed unnecessary files
2023-12-01 Removed unecessary files from motherboard
2023-12-01 Minor tweaks to motherboard
    - Changed DRC settings to allow tighter copper spacing.
    - Removed RPi 3.3V connection
2023-12-01 Added custom footprint exclusions
2023-12-02 Edited layout
2023-12-02 Edited rev2 layout
2023-12-02 deleted mounting hole and added rpi moutning hole
2023-12-02 Finished Layout rev 2
2023-12-02 Claire's Layout
    I did the layout!!!!!
2023-12-02 Final touches
2023-12-06 Added 3D model to pressure sensor
2023-12-07 Revised buck circuit and added symbol
2023-12-07 Reviced Revision (Rev.) Number
2023-12-08 Finished first version of prop control layout
2023-12-09 Cleaned up nRF schematic
2023-12-12 Uploaded nRF24 prop gerbers
2023-12-12 Reorganized stencil folder
2023-12-12 Added stencil for revised Falcon boards
2023-12-12 Added ordered power monitor gerbers
2023-12-12 Revised control and motherboard gerbers
2023-12-19 Touched up values for BOMs
2023-12-19 HTML BOMs
2024-02-03 Revised Motherboard design with correct programming pin connections
    Changed schematic with correct pins for programming and updated board to reflect this. Moved some traces to fit the new traces in.
2024-02-09 Status leds
    Added 3 status LEDs and resistors on the left side of the board. Moved some traces and vias but left all components locked in position.
2024-02-11 Fixed USB connections
2024-02-14 Updated Schematic
    Checked all connections on schematic compared to stm32f412 datasheet. Added labels for LEDs.
2024-02-14 PCB Rev2 Layout
    PCB layout revised with ground and power pours, differential routing for USB, fixes for USB and programming pins. Passes DRC.
2024-02-16 changed SWDIO pin from 38 to 34
2024-02-16 Touchups to revised control board
    - Removed redundant battery connection in schematic
    - Added labels to programming signals in schematic
    - Added "Rev. ##" label on board
2024-02-16 Touched up layout
    Updated title block and made revision label used title block value
2024-02-16 Revised control gerbers (rev 16)
2024-02-16 Order revised motherboard (rev 2)
2024-03-22 Added extra LEDs, replaced Voltage reg., added redundant SW, reviewed USB placement
    Added many new features
2024-03-23 updated 3rd revision
    reduced the number of strain gauges and updated the schematic and placed the initial layout without traces.
2024-03-23 updated flight stick schematic
2024-03-25 Touched up block diagram
    Minor changes:
    - Fixed spelling of "Strain Gauge" in a few locations
    - Changed HX711 protocol labels from "SPI" to "Digital" for accuracy
    - Fixed width of PWM arrow to the Power Assit block
    - Added number of HX711s to the flightstick block
2024-04-05 Diagram V4.0
    - Changed microcontrollers to ATtiny1616s for propellor boards
    - Added USB connection for flight stick
    - Removed power pedals that will not be present in Falcon
    - Renamed "Shaft Power" to more accurate "Shaft Strain"
2024-04-13 Specified magnetic sensor for shaft encoder
2024-04-14 Motherboard Revision 3 Initial Commit
    Motherboard updated with pull up resistors, decoupling capacitors, on board regulator, op-amp for magnetic encoder, and more.
2024-04-14 Small changes
    Cleaned up silkscreen
2024-04-15 Updated with Savo's suggested changes
2024-04-17 Updated schematic symbols
2024-04-17 Made Recommended changes
    From savo:
    C11 is a decoupling capacitor for one of the HX711s, it should be closer to it
    You can get rid of two of the mounting holes. Two are enough.
    Try to bring the USB stuff closer to the STM32, since it operates at high speed and we should keep the connections short.
    Similarly try to bring the programming header closer to the STM32.
    You can move the button stuff further from the STM32, those will be operated at kHz which is "slow"
2024-05-08 Updated Layout
    Board is now symetrical and necessary components are locked
2024-05-10 Finalilzed Layout and began routing
2024-05-11 Continued further routing
2024-05-11 Added more routing, near complete
2024-05-12 Completed Routing Draft
2024-05-13 Completed Traces and Added Graphics
2024-05-14 Touched up rev3 flight stick
    Needed to complete the 5V routing to the USB/I2C header. Also repositioned the reset button.
2024-05-17 Changed Resistor Values & Generated BOM
2024-05-22 Created Stencil with Flight Stick v3 and Motherboard v3
2024-05-24 Generated gerbers
2024-05-24 Gerbers for motherboard rev 3
2024-05-24 Changed voltage regulator footprint
    Removed thermal vias since they were too small for manufacturing.
2024-05-27 Updated flightstick gerbers to wider soldermask window
2024-06-21 increased size and updated silkscreen labels
2024-06-24 updated board shape, added silkscreen labels & new LEDs
2024-06-27 updated programmer & battery footprints
2024-06-27 updated battery & programmer footprints
2024-06-27 added width & length of board
2024-06-29 Fixed power LED labelling
    Power indication LEDs had their part references changed to labels causing DRC issues and inconsistency in the board.
    Fixed the references to be LED# again and added label text for the power lines.
2024-07-27 Began Rev4
    Changed ADC, reallocated pins, Cleaned up schematic and clear layout
2024-08-02 Reviewed Schematic and Assigned Footprints
    Changed capacitor and resistor values
    Checked all datasheets and made necessary connection changes
2024-08-03 Polishing up schematic
    - Cleaned up libraries for parts/footprints
    - Changed page and updated titleblock
    - Changed symbol to reflect new microcontroller selection
    - Updated symbols to modern KiCad variants
2024-08-03 Began Layout
    Started Layout no routing
    Added RGB LED
    Changed footprints
2024-08-06 Finalized Component Placement
    Finished Component Placement
    Changed switch
2024-08-07 Started on the Routing
    layout component placement requires review, traces placed
    MCU pins re-assigned
2024-08-10 Completed First Draft
    Completed Routing
    Checked DRC
    Fixed All DRC issues
    Did not resolve ADC clearance issues
2024-08-10 Reorganized Schematic
2024-08-10 Touchups
    - Added GND pour on top
    - Cleaned up some traces
    - Fixed 3V3 missing connections
    - Reduced pad size on ADC for clearance
    - Removed last vias in pads
2024-08-11 Updated Layout, Added Assembly part #s
    Cleaned up layout for assembly minimum spacing
    Added JLCPCB part #s for preorder and manufacturing
2024-08-12 Ammended DRC Violations
2024-08-12 Update production specifications of connectors and mounting holes
2024-08-14 FINISHED AND ORDERED DAT HOE
    REV 4 COMPLETED, GERBER FILES PRODUCED, ASSEMBLY SUBMITTED
2024-08-14 being silly
2024-08-17 Completed spar sensor revised schematic
2024-08-17 Completed PCB layout of ATtiny1616 based strain gauge board
2025-08-14 update rev4 to prod model
2025-08-14 Created Draft of rev5 with CAN
2025-08-16 Moving REV5 to new repo
    moving to hpvdt/falcon_flight_stick
2025-08-17 Recording obsolesence
